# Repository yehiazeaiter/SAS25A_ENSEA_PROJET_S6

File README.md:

# SAS25A_ENSEA_PROJET_S6

This repository contains the code and documentation for our first year school project. An embedded systems project using STM32CubeIDE to build a robot that plays hide and seek in a labyrinth using motors for moving, an ultrasonic sensor for obstacle detection, and an infrared sensor for detecting the other playing robot.

## Table of Contents
- [Project Overview](#project-overview)
- [Team Members](#team-members)
- [Folder Structure](#folder-structure)

## Project Overview

This embedded systems project aimed to build a robot capable of playing a game of hide-and-seek using sensors and motor control, based on the STM32L476RG microcontroller, in a compact design with an integrated PCB.

### What We Achieved
- The robot can **move forward** using DC motors
- It **stops automatically** when an obstacle is detected via the ultrasonic sensor
- It **blinks an LED** when receiving a signal from the infrared receiver
- A PCB design ready to print

### What Was Not Fully Implemented
- Autonomous hide-and-seek behavior
- Navigation or decision-making logic
- Compact design with an integrated PCB

Despite not reaching the original goal, the project successfully integrates core embedded system concepts such as motor control, sensor interfacing, and interrupt-based signaling.

## Team Members

- BELLAHBIB Amate-Allah 
- EL MESTARI Mohamed-Amine 
- NASSCHAERT Florent 
- PERRIN Maël 
- ZEAITER Yehia 

### Contributions

| Member       | Contributions Summary                                                                                   |                    
|--------------|---------------------------------------------------------------------------------------------------------|
| Amate-Allah  | PCB design, infrared sensor testing, final presentation, final report                                   |
| Mohamed-Amine| Ultrasonic sensor testing, weekly reports, final report                                                 |
| Florent      | Infrared sensor testing, programming, timer setup, algorithm diagram                                    |
| Maël         | Stepper motors testing, 3D modeling, GANTT diagram                                                      |
| Yehia        | Ultrasonic sensor testing, DC and stepper motors testing, timer setup, SADT diagram, task distribution  |

## Folder structure
- `project files/`: KiCad and STM32CubeIDE project files
- `how to guides/`: guides on how to achieve the different tasks done in the project

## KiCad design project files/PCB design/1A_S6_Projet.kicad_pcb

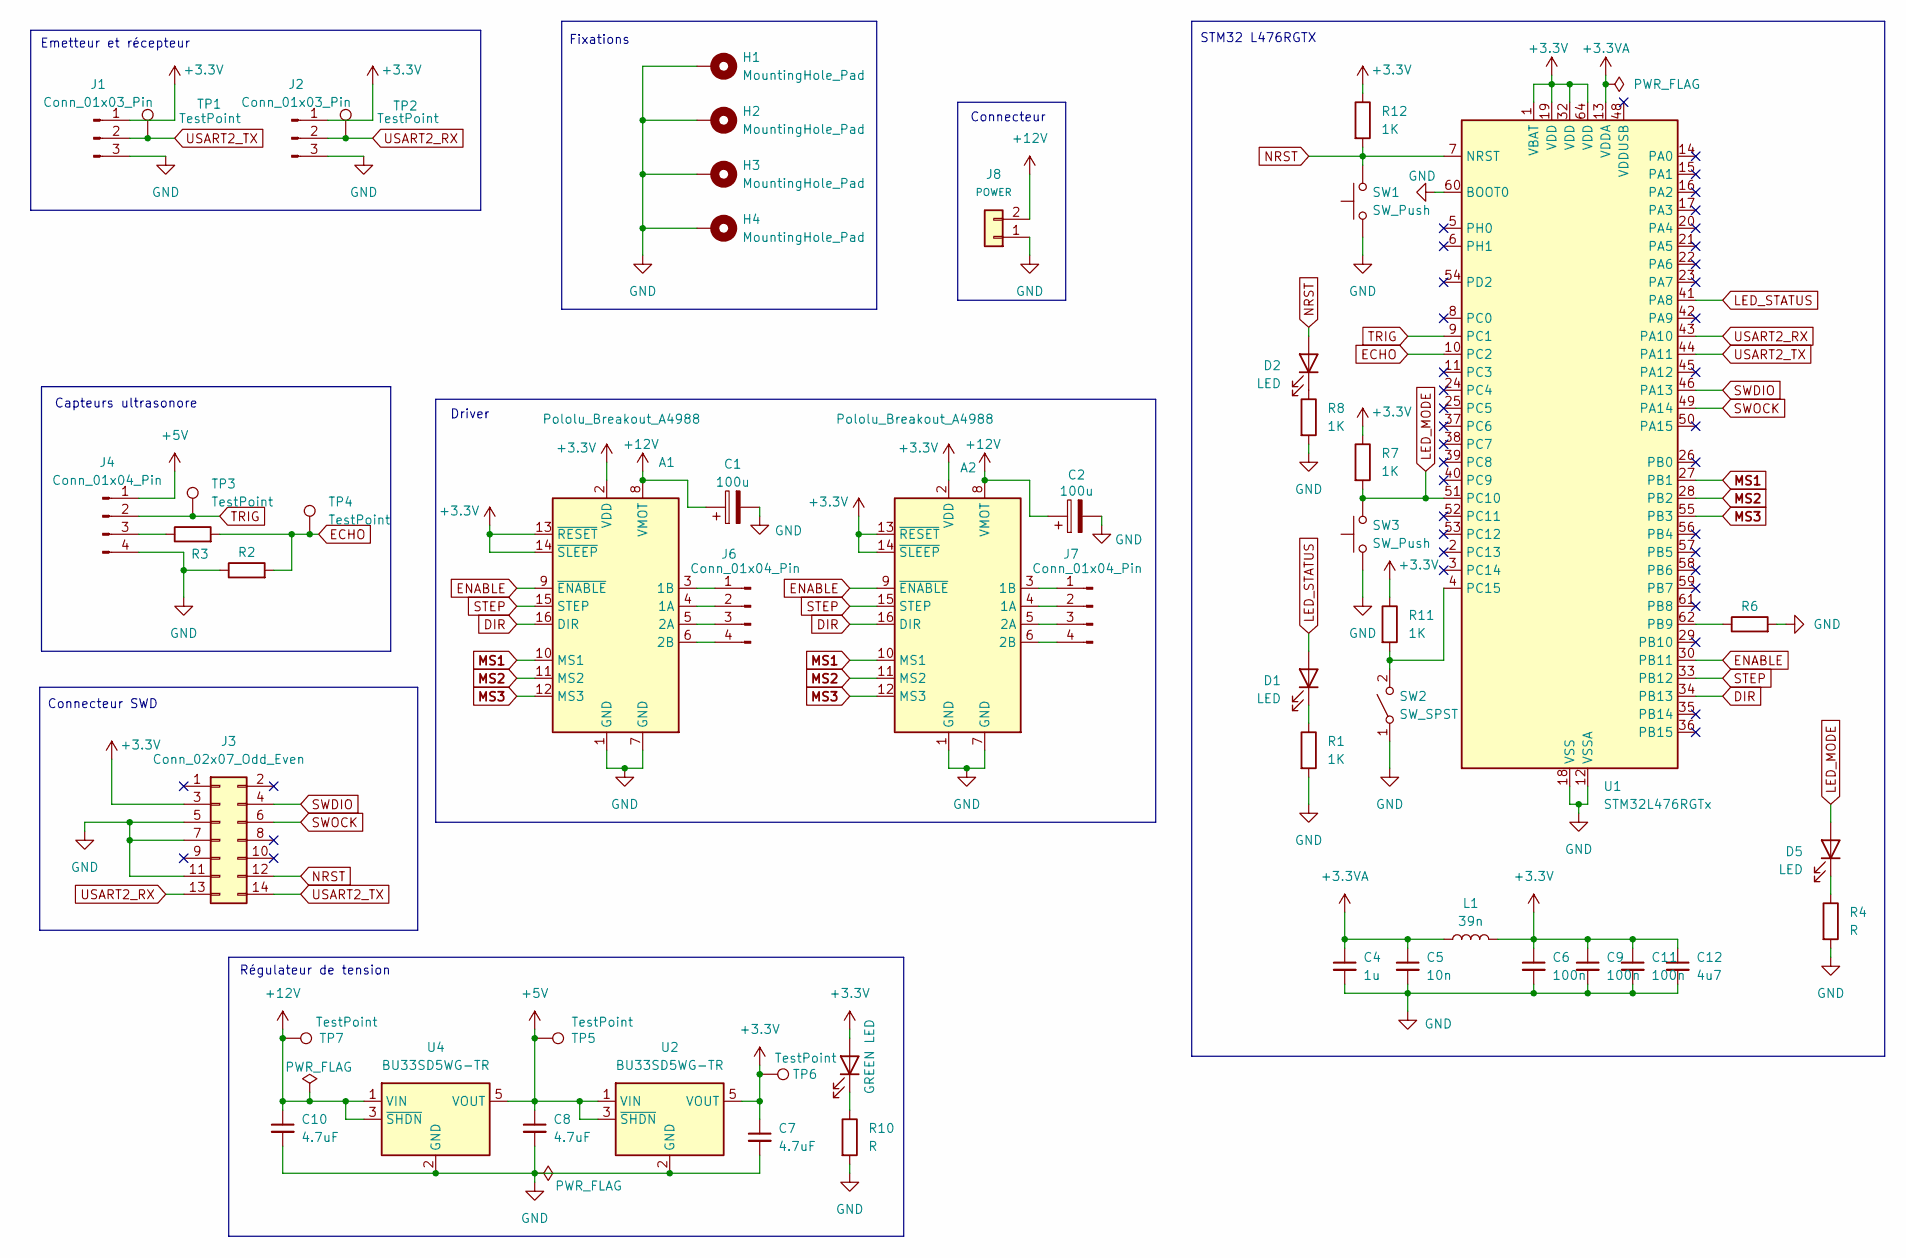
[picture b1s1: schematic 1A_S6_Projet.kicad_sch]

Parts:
A1, A2: Pololu_Breakout_A4988; Pololu_Breakout-16_15.2x20.3mm
C1, C2: 100u; CP_Elec_8x10.5
C4: 1u; C_1206_3216Metric_Pad1.33x1.80mm_HandSolder
C5: 10n; C_0805_2012Metric_Pad1.18x1.45mm_HandSolder
C6, C9, C11: 100n; C_1206_3216Metric_Pad1.33x1.80mm_HandSolder
C7, C8, C10: 4.7uF; C_1206_3216Metric_Pad1.33x1.80mm_HandSolder
C12: 4u7; C_1206_3216Metric_Pad1.33x1.80mm_HandSolder
D1, D2, D5: LED; LED_0603_1608Metric_Pad1.05x0.95mm_HandSolder
D4: GREEN LED; LED_0603_1608Metric_Pad1.05x0.95mm_HandSolder
H1, H2, H3, H4: MountingHole_Pad; MountingHole_3.2mm_M3_DIN965_Pad
J1, J2: Conn_01x03_Pin; JST_XH_B3B-XH-A_1x03_P2.50mm_Vertical
J3: Conn_02x07_Odd_Even; PinHeader_2x07_P1.27mm_Vertical_SMD
J4, J6, J7: Conn_01x04_Pin; JST_XH_B4B-XH-A_1x04_P2.50mm_Vertical
J8: POWER; JST_XH_B2B-XH-A_1x02_P2.50mm_Vertical
L1: 39n; L_0805_2012Metric_Pad1.05x1.20mm_HandSolder
R1, R3, R6, R7, R8, R11, R12: 1K; R_0603_1608Metric_Pad0.98x0.95mm_HandSolder
R2: 2K; R_0603_1608Metric_Pad0.98x0.95mm_HandSolder
R4, R10: R; R_0603_1608Metric_Pad0.98x0.95mm_HandSolder
SW1, SW3: SW_Push; SW_Push_1P1T_NO_CK_KMR2
SW2: SW_SPST; SW_Push_1P1T_NO_CK_KMR2
TP1, TP2, TP3, TP4, TP5, TP6, TP7: TestPoint; TestPoint_Pad_D1.0mm
U1: STM32L476RGTx; LQFP-64_10x10mm_P0.5mm
U2, U4: BU33SD5WG-TR; SOT-23-5

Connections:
+3.3V: A1.2 (VDD), A1.13 (~RESET), A1.14 (~SLEEP), A2.2 (VDD), A2.13 (~RESET), A2.14 (~SLEEP), C6.1, C7.1, C9.1, C11.1, C12.1, D4.2 (A), J1.1, J2.1, J3.3, L1.2, R7.1, R11.1, R12.1, TP6.1, U1.1 (VBAT), U1.19 (VDD), U1.32 (VDD), U1.64 (VDD), U2.5 (VOUT)
+3.3VA: C4.1, C5.1, L1.1, U1.13 (VDDA)
+5V: C8.1, J4.1, TP5.1, U2.1 (VIN), U2.3 (~SHDN), U4.5 (VOUT)
+12V: A1.8 (VMOT), A2.8 (VMOT), C1.1, C2.1, C10.1, J8.2, TP7.1, U4.1 (VIN), U4.3 (~SHDN)
DIR: A1.16 (DIR), A2.16 (DIR), U1.34 (PB13)
ECHO: R2.2, R3.2, TP4.1, U1.10 (PC2)
ENABLE: A1.9 (~ENABLE), A2.9 (~ENABLE), U1.30 (PB11)
GND: A1.1 (GND), A1.7 (GND), A2.1 (GND), A2.7 (GND), C1.2, C2.2, C4.2, C5.2, C6.2, C7.2, C8.2, C9.2, C10.2, C11.2, C12.2, H1.1, H2.1, H3.1, H4.1, J1.3, J2.3, J3.5, J3.7, J3.11, J4.4, J8.1, R1.2, R2.1, R4.2, R6.2, R8.2, R10.2, SW1.1, SW2.1 (A), SW3.1, U1.12 (VSSA), U1.18 (VSS), U1.31 (VSS), U1.47 (VSS), U1.60 (BOOT0), U1.63 (VSS), U2.2 (GND), U4.2 (GND)
LED_MODE: D5.2 (A), R7.2, SW3.2, U1.51 (PC10)
LED_STATUS: D1.2 (A), U1.41 (PA8)
MS1: A1.10 (MS1), A2.10 (MS1), U1.27 (PB1)
MS2: A1.11 (MS2), A2.11 (MS2), U1.28 (PB2)
MS3: A1.12 (MS3), A2.12 (MS3), U1.55 (PB3)
NRST: D2.2 (A), J3.12, R12.2, SW1.2, U1.7 (NRST)
unnamed: A1.4 (1A), J6.2
unnamed: A1.3 (1B), J6.1
unnamed: A1.5 (2A), J6.3
unnamed: A1.6 (2B), J6.4
unnamed: A2.4 (1A), J7.2
unnamed: A2.3 (1B), J7.1
unnamed: A2.5 (2A), J7.3
unnamed: A2.6 (2B), J7.4
unnamed: D1.1 (K), R1.1
unnamed: D2.1 (K), R8.1
unnamed: D4.1 (K), R10.1
unnamed: D5.1 (K), R4.1
unnamed: J4.3, R3.1
unnamed: R11.2, SW2.2 (B), U1.4 (PC15)
unnamed: R6.1, U1.62 (PB9)
STEP: A1.15 (STEP), A2.15 (STEP), U1.33 (PB12)
SWDIO: J3.4, U1.46 (PA13)
SWOCK: J3.6, U1.49 (PA14)
TRIG: J4.2, TP3.1, U1.9 (PC1)
USART2_RX: J2.2, J3.13, TP2.1, U1.43 (PA10)
USART2_TX: J1.2, J3.14, TP1.1, U1.44 (PA11)

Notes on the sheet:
Capteurs ultrasonore
STM32 L476RGTX
Fixations
Régulateur de tension
Connecteur
Connecteur SWD
Driver
Emetteur et récepteur

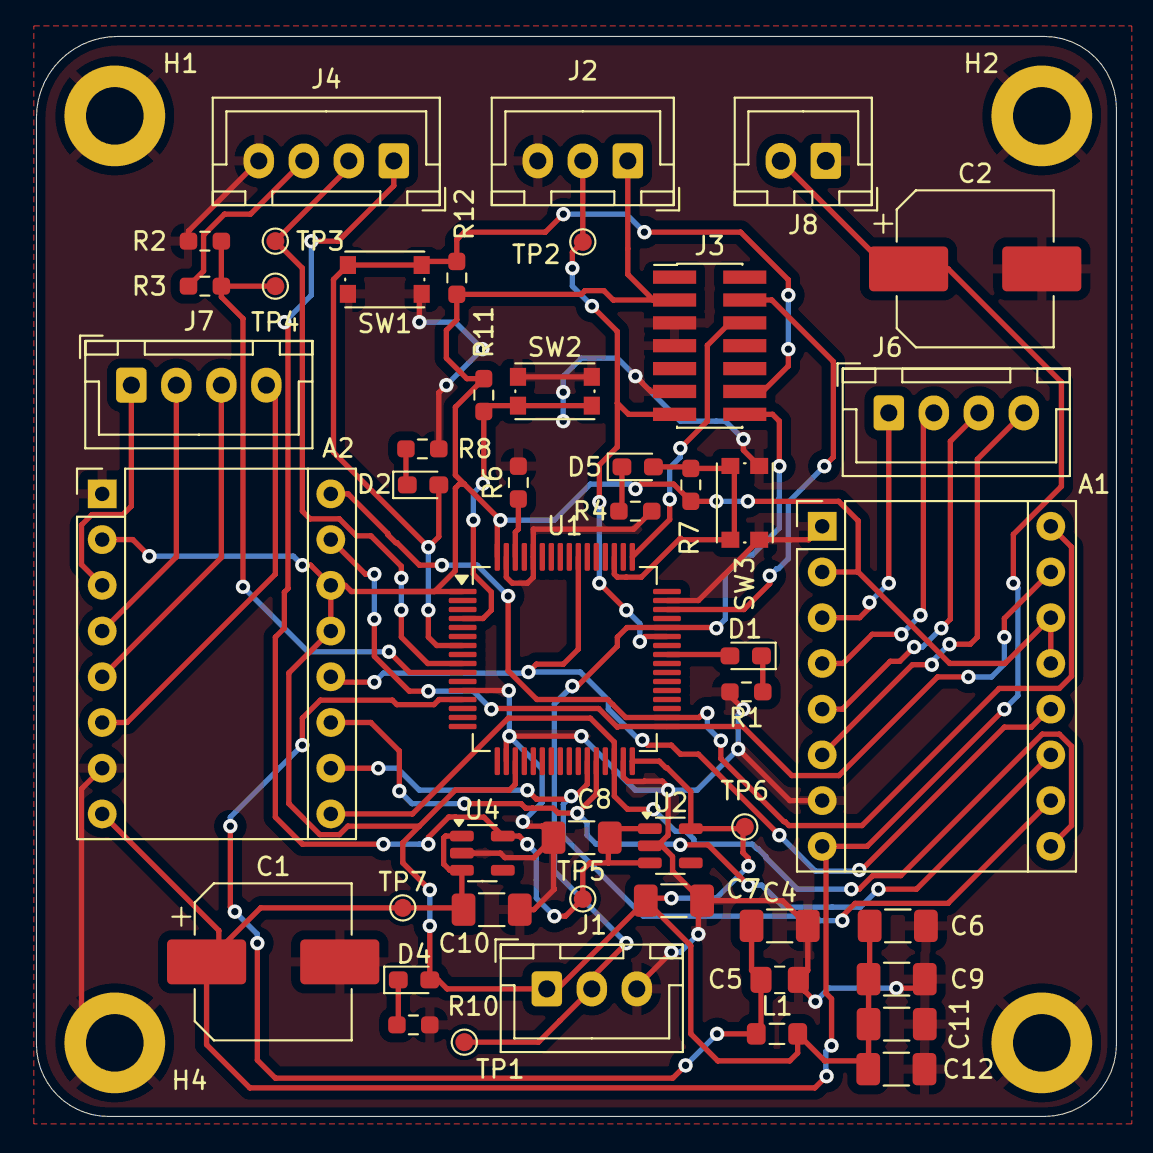
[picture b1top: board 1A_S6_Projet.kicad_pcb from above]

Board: 2 copper layers, 60.0 x 60.0 mm, 52 parts (0 on the bottom side), 35 nets.

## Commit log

2025-06-02 Create poster
2025-06-03 Rename PCB.md to 1A_PCB.md
2025-06-03 Rename STM.md to $STM.md
2025-06-03 Create dc_motors
